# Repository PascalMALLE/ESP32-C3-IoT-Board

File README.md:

<<<<<<< HEAD
# ESP32-C3-IoT-Board
Board ESP32 IoT board for learning Kicad
=======
# ESP32-C3 IoT Development Board

A custom-designed IoT development board built around the **ESP32-C3-02**, featuring USB-C connectivity, Li-ion battery charging, environmental sensing, audio input, and removable storage.

## Project Overview

This project focuses on the design of a compact, custom PCB for IoT applications using KiCad. The board integrates wireless connectivity, power management, sensors, and data storage into a single hardware platform.

## Key Features

- **Microcontroller:** ESP32-C3-02 with Wi-Fi and Bluetooth Low Energy (BLE).
- **Power Management:** TP4056-based single-cell Li-ion battery charging.
- **USB-C:** USB connectivity and power input.
- **Environmental Sensing:** BME280 for temperature, humidity, and atmospheric pressure.
- **Audio Input:** Onboard microphone for sound acquisition.
- **Data Storage:** MicroSD card interface and additional flash memory.
- **Display Interface:** I²C interface for an optional OLED display.
- **Status Indicators:** LEDs for power and charging status.
- **Expansion:** Interfaces for additional sensors and peripherals.

## Hardware Design

### 1. Schematic

The schematic defines the electrical connections between the ESP32-C3-02, charging circuit, sensors, storage interfaces, and peripheral connectors.

### 2. PCB Layout

The PCB layout implements the circuit connections, component placement, routing, and board geometry.

| Front Side | Bottom Side |
|---|---|
|  |  |

### 3. 3D PCB Visualization

The 3D model provides a visual representation of the assembled PCB and component placement.

## Design Highlights

- Compact PCB layout designed in KiCad.
- USB-C and rechargeable Li-ion battery power options.
- Integrated wireless connectivity through the ESP32-C3.
- Sensor interfaces for environmental and audio data acquisition.
- MicroSD storage for data logging applications.
- Design files available for inspection and further development.

## Repository Contents

- **KiCad schematic:** `.kicad_sch`
- **KiCad PCB layout:** `.kicad_pcb`
- **3D visualizations:** PCB rendering images.
- **Gerber files:** Manufacturing output files, when included.
- **Bill of Materials (BOM):** Component list and procurement information.
- **Documentation:** Design screenshots and supporting resources.

## Tools

- KiCad
- PCB design and routing
- Electronic schematic capture
- 3D PCB visualization

## Potential Applications

- IoT environmental monitoring
- Portable data logging
- Wireless sensor nodes
- Embedded systems prototyping

## Project Status

PCB design and visualization completed. Hardware manufacturing, assembly, and functional validation should be documented as those stages are completed.

## Author

**Pascal Malle**

Electrical, Electronic and Telecommunications Engineering

---

*This project is intended for learning, prototyping, and further development. Verify the charging and battery-protection circuitry against the selected components' datasheets before manufacturing or powering the board.*
>>>>>>> 4541118 (Add ESP32-C3 IoT PCB design)

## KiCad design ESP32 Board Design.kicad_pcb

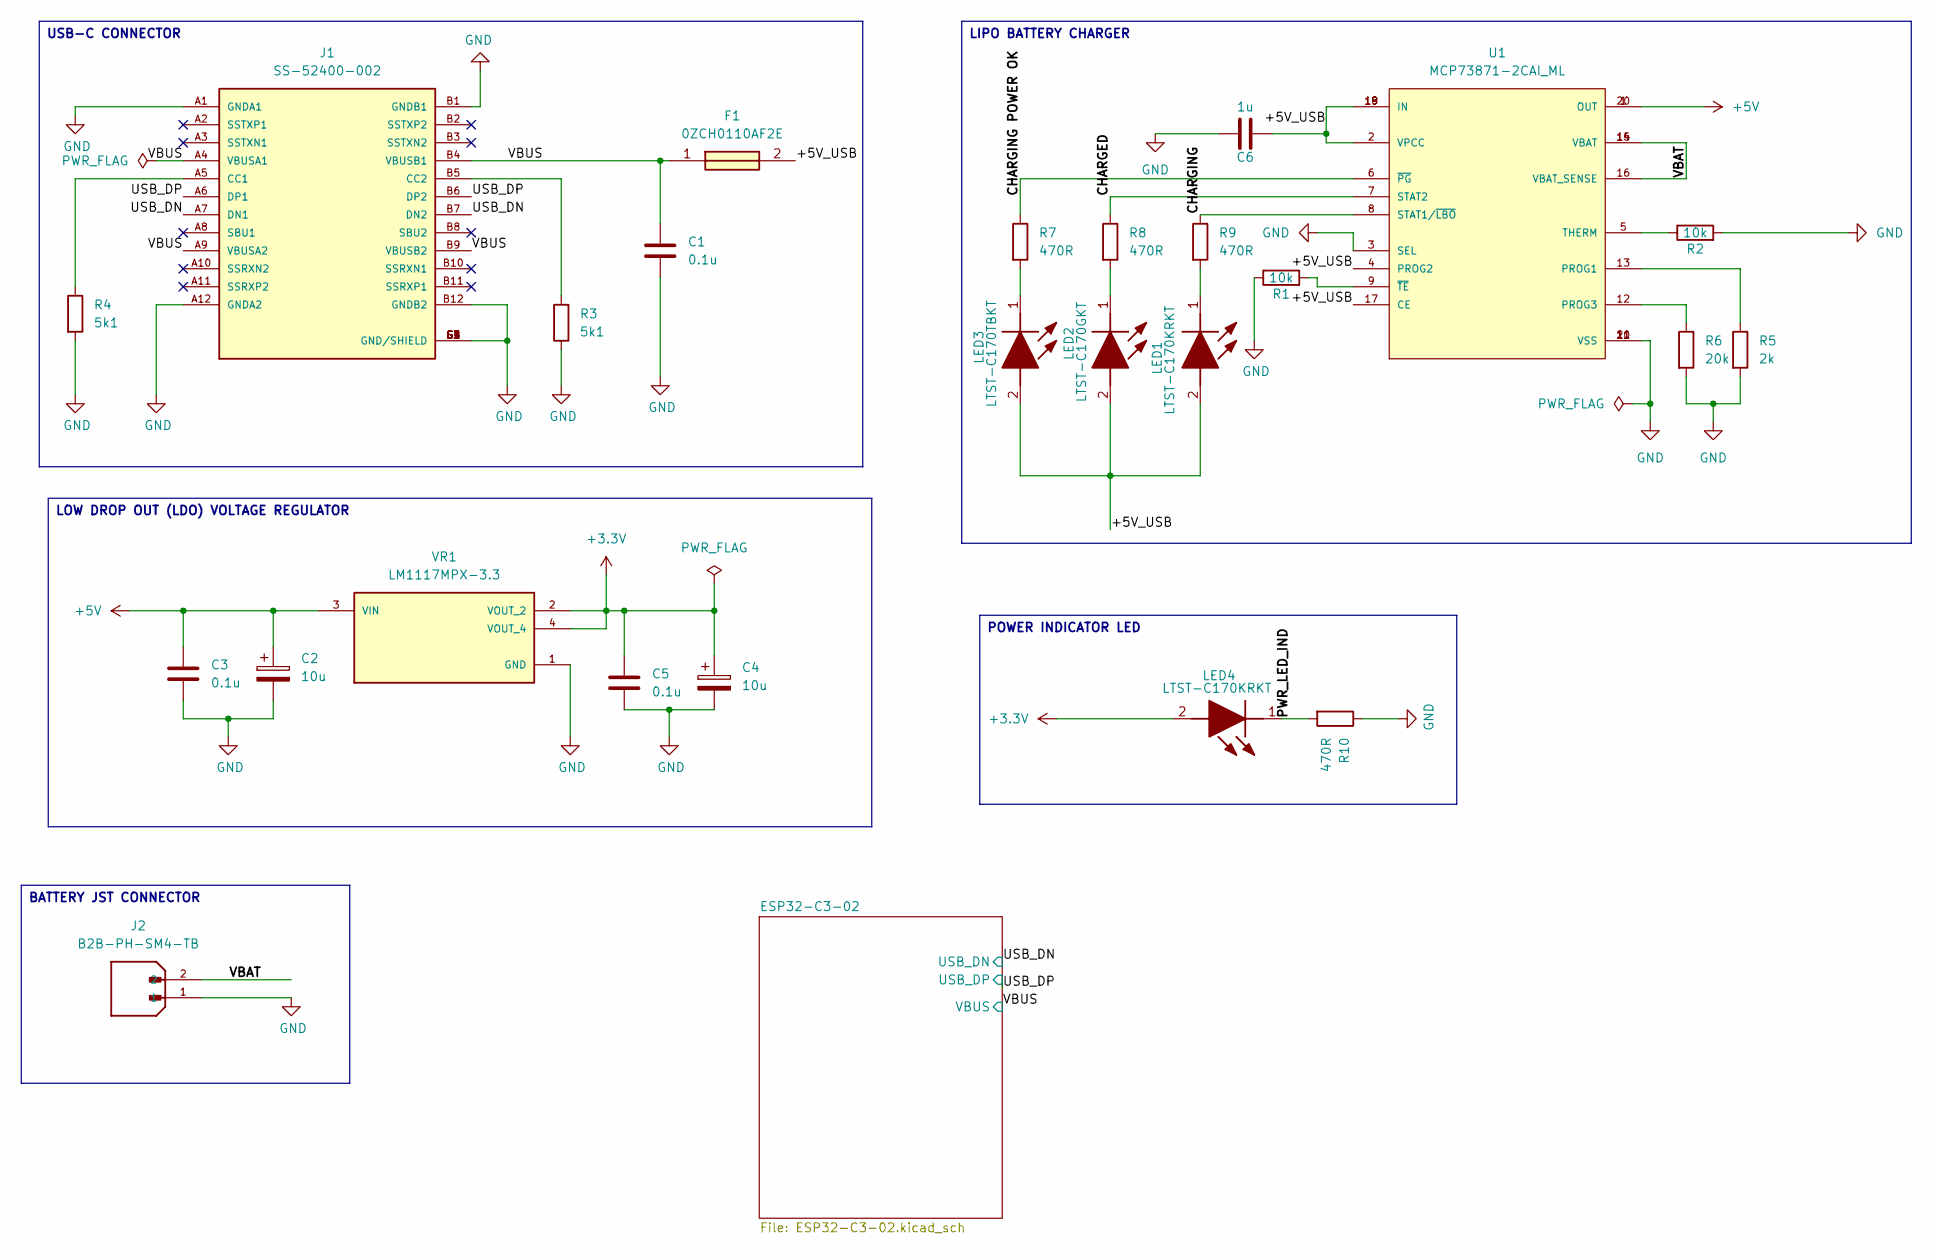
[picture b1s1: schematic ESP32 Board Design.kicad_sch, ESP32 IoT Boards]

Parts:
C1, C3, C5: 0.1u; C_0805_2012Metric
C2, C4: 10u; T491A
C6: 1u; C_0805_2012Metric
F1: 0ZCH0110AF2E; FUSC3226X100N; Manufacturer_Part_Number 0ZCH0110AF2E
J1: SS-52400-002; BELFUSE_SS-52400-002; PARTREV A0
J2: B2B-PH-SM4-TB; JST_B2B-PH-SM4-TB; PARTREV N/A
LED1, LED4: LTST-C170KRKT; LEDC2012X120N; Manufacturer_Part_Number LTST-C170KRKT; Mouser Part Number 859-LTST-C170KRKT
LED2: LTST-C170GKT; LEDC2012X120N; Manufacturer_Part_Number LTST-C170GKT; Mouser Part Number 859-LTST-C170GKT
LED3: LTST-C170TBKT; LEDC2012X120N; Manufacturer_Part_Number LTST-C170TBKT; Mouser Part Number 859-LTST-C170TBKT
R1, R2: 10k; R_0805_2012Metric
R3, R4: 5k1; R_0805_2012Metric
R5: 2k; R_0805_2012Metric
R6: 20k; R_0805_2012Metric
R7, R8, R9, R10: 470R; R_0805_2012Metric
U1: MCP73871-2CAI_ML; QFN50P400X400X100-21N; PARTREV D
VR1: LM1117MPX-3.3; VREG_LM1117MPX-3.3

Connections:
+3.3V: C4.1, C5.1, LED4.2 (A), VR1.2 (VOUT_2), VR1.4 (VOUT_4); also elsewhere on the board
+5V: C2.1, C3.1, U1.1 (OUT), U1.20 (OUT), VR1.3 (VIN)
/+5V_USB: C6.2, F1.2, LED1.2 (A), LED2.2 (A), LED3.2 (A), U1.2 (VPCC), U1.4 (PROG2), U1.17 (CE), U1.18 (IN), U1.19 (IN)
/CHARGED: R8.1, U1.7 (STAT2)
/CHARGING: R9.1, U1.8 (STAT1/~LBO)
/CHARGING POWER OK: R7.1, U1.6 (~PG)
/PWR_LED_IND: LED4.1 (K), R10.2; also elsewhere on the board
/USB_DN: J1.A7 (DN1), J1.B7 (DN2); also elsewhere on the board
/USB_DP: J1.A6 (DP1), J1.B6 (DP2); also elsewhere on the board
/VBAT: J2.2, U1.14 (VBAT), U1.15 (VBAT), U1.16 (VBAT_SENSE)
/VBUS: C1.1, F1.1, J1.A4 (VBUSA1), J1.A9 (VBUSA2), J1.B4 (VBUSB1), J1.B9 (VBUSB2); also elsewhere on the board
GND: C1.2, C2.2, C3.2, C4.2, C5.2, C6.1, J1.A1 (GNDA1), J1.A12 (GNDA2), J1.B1 (GNDB1), J1.B12 (GNDB2), J1.G1 (GND/SHIELD), J1.G2 (GND/SHIELD), J1.G3 (GND/SHIELD), J1.G4 (GND/SHIELD), J1.S1 (GND/SHIELD), J1.S2 (GND/SHIELD), J1.S3 (GND/SHIELD), J1.S4 (GND/SHIELD), J2.1, R1.1, R2.2, R3.1, R4.2, R5.2, R6.2, R10.1, U1.3 (SEL), U1.10 (VSS), U1.11 (VSS), U1.21 (VSS), VR1.1 (GND); also elsewhere on the board
unnamed: J1.A5 (CC1), R4.1
unnamed: J1.B5 (CC2), R3.2
unnamed: LED1.1 (K), R9.2
unnamed: LED2.1 (K), R8.2
unnamed: LED3.1 (K), R7.2
unnamed: R5.1, U1.13 (PROG1)
unnamed: R6.1, U1.12 (PROG3)
unnamed: R2.1, U1.5 (THERM)
unnamed: R1.2, U1.9 (~TE)

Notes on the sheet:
BATTERY JST CONNECTOR
USB-C CONNECTOR
LIPO BATTERY CHARGER
POWER INDICATOR LED
LOW DROP OUT (LDO) VOLTAGE REGULATOR

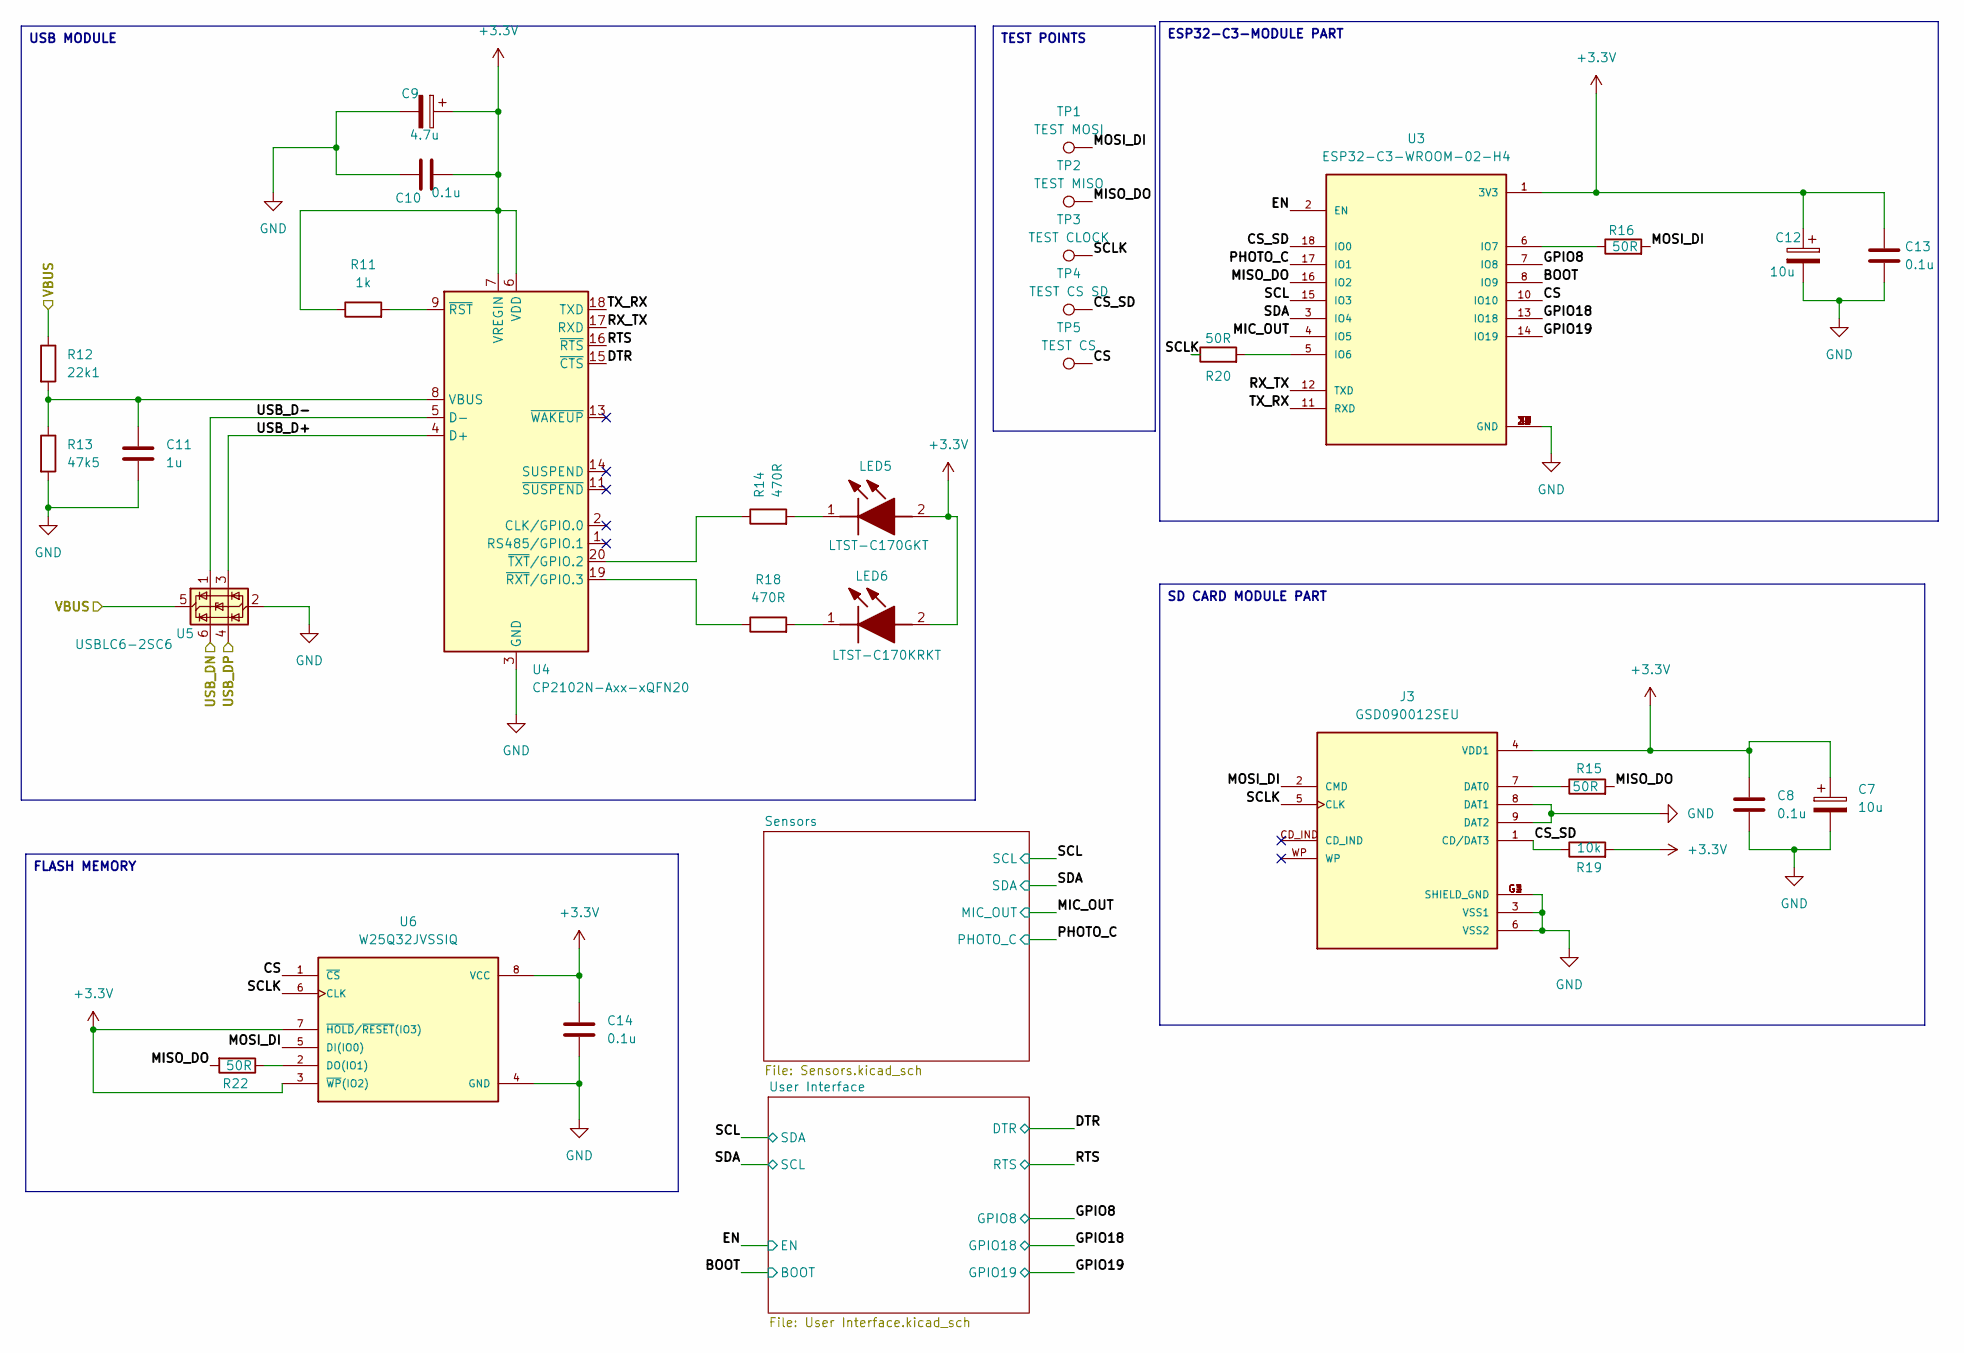
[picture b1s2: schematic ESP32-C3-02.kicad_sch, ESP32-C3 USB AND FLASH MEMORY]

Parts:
C7, C12: 10u; T491A
C8, C10, C13, C14: 0.1u; C_0805_2012Metric
C9: 4.7u; T491A
C11: 1u; C_0805_2012Metric
J3: GSD090012SEU; AMPHENOL_GSD090012SEU; PARTREV E
LED5: LTST-C170GKT; LEDC2012X120N; Manufacturer_Part_Number LTST-C170GKT; Mouser Part Number 859-LTST-C170GKT
LED6: LTST-C170KRKT; LEDC2012X120N; Manufacturer_Part_Number LTST-C170KRKT; Mouser Part Number 859-LTST-C170KRKT
R11: 1k; R_0805_2012Metric
R12: 22k1; R_0805_2012Metric
R13: 47k5; R_0805_2012Metric
R14, R18: 470R; R_0805_2012Metric
R15, R16, R20, R22: 50R; R_0805_2012Metric
R19: 10k; R_0805_2012Metric
TP1: TEST MOSI; TestPoint_Pad_D1.0mm
TP2: TEST MISO; TestPoint_Pad_D1.0mm
TP3: TEST CLOCK; TestPoint_Pad_D1.0mm
TP4: TEST CS SD; TestPoint_Pad_D1.0mm
TP5: TEST CS; TestPoint_Pad_D1.0mm
U3: ESP32-C3-WROOM-02-H4; MODULE_ESP32-C3-WROOM-02-H4
U4: CP2102N-Axx-xQFN20; SiliconLabs_QFN-20-1EP_3x3mm_P0.5mm_EP1.8x1.8mm
U5: USBLC6-2SC6; SOT-23-6
U6: W25Q32JVSSIQ; SOIC127P790X216-8N; M_PART_NUMBER W25QXX

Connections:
+3.3V: C7.1, C8.1, C9.1, C10.2, C12.1, C13.1, C14.1, J3.4 (VDD1), LED5.2 (A), LED6.2 (A), R11.1, R19.2, U3.1 (3V3), U4.6 (VDD), U4.7 (VREGIN), U6.3 (~WP(IO2)), U6.7 (~HOLD/~RESET(IO3)), U6.8 (VCC); also elsewhere on the board
/ESP32-C3-02/BOOT: U3.8 (IO9); also elsewhere on the board
/ESP32-C3-02/CS: TP5.1 (1_1), U3.10 (IO10), U6.1 (~CS)
/ESP32-C3-02/CS_SD: J3.1 (CD/DAT3), R19.1, TP4.1 (1_1), U3.18 (IO0)
/ESP32-C3-02/DTR: U4.15 (~CTS); also elsewhere on the board
/ESP32-C3-02/EN: U3.2 (EN); also elsewhere on the board
/ESP32-C3-02/GPIO8: U3.7 (IO8); also elsewhere on the board
/ESP32-C3-02/GPIO18: U3.13 (IO18); also elsewhere on the board
/ESP32-C3-02/GPIO19: U3.14 (IO19); also elsewhere on the board
/ESP32-C3-02/MIC_OUT: U3.4 (IO5); also elsewhere on the board
/ESP32-C3-02/MISO_DO: R15.2, R22.2, TP2.1 (1_1), U3.16 (IO2)
/ESP32-C3-02/MOSI_DI: J3.2 (CMD), R16.2, TP1.1 (1_1), U6.5 (DI(IO0))
/ESP32-C3-02/PHOTO_C: U3.17 (IO1); also elsewhere on the board
/ESP32-C3-02/RTS: U4.16 (~RTS); also elsewhere on the board
/ESP32-C3-02/RX_TX: U3.12 (TXD), U4.17 (RXD)
/ESP32-C3-02/SCL: U3.15 (IO3); also elsewhere on the board
/ESP32-C3-02/SCLK: J3.5 (CLK), R20.1, TP3.1 (1_1), U6.6 (CLK)
/ESP32-C3-02/SDA: U3.3 (IO4); also elsewhere on the board
/ESP32-C3-02/TX_RX: U3.11 (RXD), U4.18 (TXD)
/ESP32-C3-02/USB_D+: U4.4 (D+), U5.3 (I/O2)
/ESP32-C3-02/USB_D-: U4.5 (D-), U5.1 (I/O1)
/USB_DN: U5.6 (I/O1); also elsewhere on the board
/USB_DP: U5.4 (I/O2); also elsewhere on the board
/VBUS: R12.1, U5.5 (VBUS); also elsewhere on the board
GND: C7.2, C8.2, C9.2, C10.1, C11.2, C12.2, C13.2, C14.2, J3.3 (VSS1), J3.6 (VSS2), J3.8 (DAT1), J3.9 (DAT2), J3.G1 (SHIELD_GND), J3.G2 (SHIELD_GND), J3.G3 (SHIELD_GND), J3.G4 (SHIELD_GND), R13.2, U3.9 (GND), U3.19 (GND), U3.20 (GND), U3.21 (GND), U3.22 (GND), U3.23 (GND), U3.24 (GND), U3.25 (GND), U3.26 (GND), U3.27 (GND), U3.28 (GND), U3.29 (GND), U3.30 (GND), U3.31 (GND), U3.32 (GND), U3.33 (GND), U3.34 (GND), U3.35 (GND), U3.36 (GND), U3.37 (GND), U3.38 (GND), U3.39 (GND), U4.3 (GND), U4.12 (GND), U4.21 (GND), U5.2 (GND), U6.4 (GND); also elsewhere on the board
unnamed: J3.7 (DAT0), R15.1
unnamed: LED5.1 (K), R14.2
unnamed: LED6.1 (K), R18.2
unnamed: R20.2, U3.5 (IO6)
unnamed: R16.1, U3.6 (IO7)
unnamed: C11.1, R12.2, R13.1, U4.8 (VBUS)
unnamed: R11.2, U4.9 (~RST)
unnamed: R18.1, U4.19 (~RXT/GPIO.3)
unnamed: R14.1, U4.20 (~TXT/GPIO.2)
unnamed: R22.1, U6.2 (DO(IO1))

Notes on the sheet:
ESP32-C3-MODULE PART
TEST POINTS
FLASH MEMORY
SD CARD MODULE PART
USB MODULE

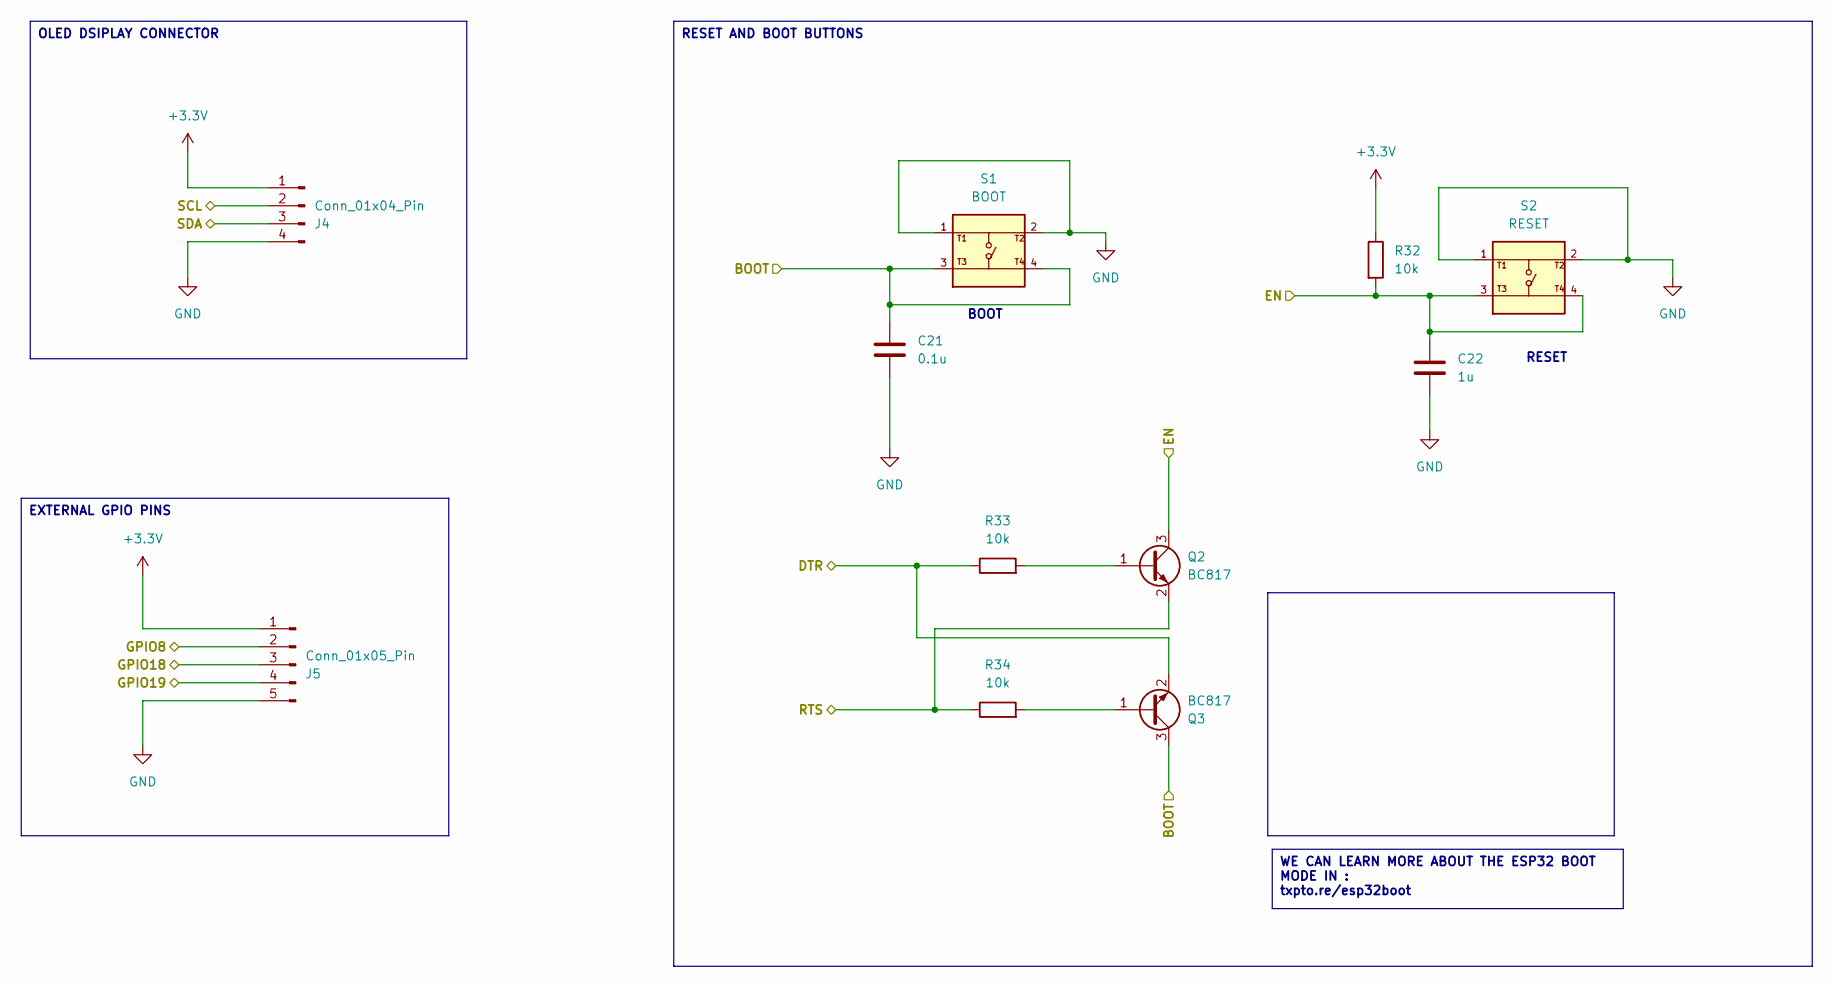
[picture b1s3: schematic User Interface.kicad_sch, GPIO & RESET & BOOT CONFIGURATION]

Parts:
C21: 0.1u; C_0805_2012Metric
C22: 1u; C_0805_2012Metric
J4: Conn_01x04_Pin; PinHeader_1x04_P2.54mm_Vertical
J5: Conn_01x05_Pin; PinHeader_1x05_P2.54mm_Vertical
Q2, Q3: BC817; SOT-23
R32, R33, R34: 10k; R_0805_2012Metric
S1: BOOT; SW_USLPT2819DT2TR; PARTREV P
S2: RESET; SW_USLPT2819DT2TR; PARTREV P

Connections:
+3.3V: J4.1, J5.1, R32.1; also elsewhere on the board
/ESP32-C3-02/BOOT: C21.1, Q3.3 (C), S1.3, S1.4; also elsewhere on the board
/ESP32-C3-02/DTR: Q3.2 (E), R33.1; also elsewhere on the board
/ESP32-C3-02/EN: C22.1, Q2.3 (C), R32.2, S2.3, S2.4; also elsewhere on the board
/ESP32-C3-02/GPIO8: J5.2; also elsewhere on the board
/ESP32-C3-02/GPIO18: J5.3; also elsewhere on the board
/ESP32-C3-02/GPIO19: J5.4; also elsewhere on the board
/ESP32-C3-02/RTS: Q2.2 (E), R34.1; also elsewhere on the board
/ESP32-C3-02/SCL: J4.3; also elsewhere on the board
/ESP32-C3-02/SDA: J4.2; also elsewhere on the board
GND: C21.2, C22.2, J4.4, J5.5, S1.1, S1.2, S2.1, S2.2; also elsewhere on the board
unnamed: Q2.1 (B), R33.2
unnamed: Q3.1 (B), R34.2

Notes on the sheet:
BOOT
RESET
OLED DSIPLAY CONNECTOR
EXTERNAL GPIO PINS
WE CAN LEARN MORE ABOUT THE ESP32 BOOT MODE IN : txpto.re/esp32boot
RESET AND BOOT BUTTONS

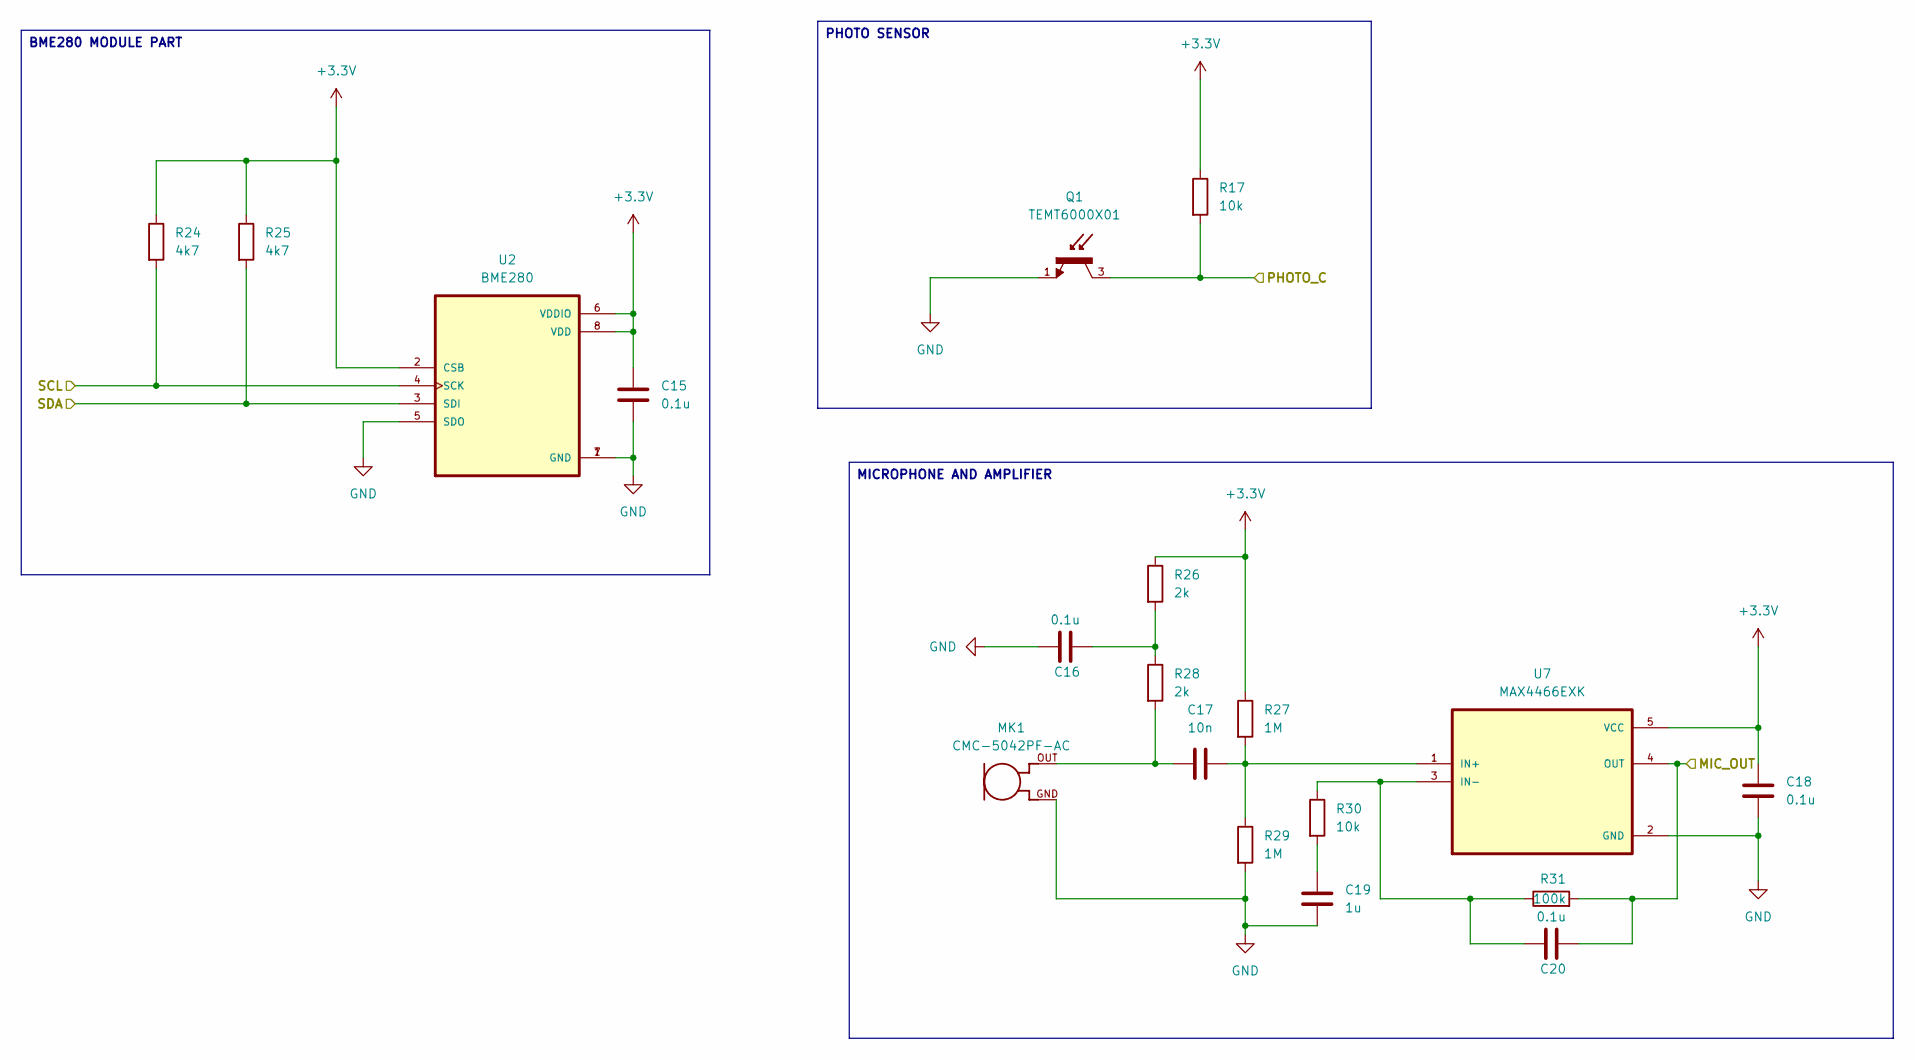
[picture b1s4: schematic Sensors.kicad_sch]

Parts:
C15, C16, C18, C20: 0.1u; C_0805_2012Metric
C17: 10n; C_0805_2012Metric
C19: 1u; C_0805_2012Metric
MK1: CMC-5042PF-AC; CUI_CMC-5042PF-AC
Q1: TEMT6000X01; TRANS_TEMT6000X01; PARTREV 1.9
R17, R30: 10k; R_0805_2012Metric
R24, R25: 4k7; R_0805_2012Metric
R26, R28: 2k; R_0805_2012Metric
R27, R29: 1M; R_0805_2012Metric
R31: 100k; R_0805_2012Metric
U2: BME280; PSON65P250X250X100-8N
U7: MAX4466EXK; SOT65P210X110-5N

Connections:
+3.3V: C15.1, C18.1, R17.1, R24.1, R25.1, R26.1, R27.1, U2.2 (CSB), U2.6 (VDDIO), U2.8 (VDD), U7.5 (VCC); also elsewhere on the board
/ESP32-C3-02/MIC_OUT: C20.2, R31.2, U7.4 (OUT); also elsewhere on the board
/ESP32-C3-02/PHOTO_C: Q1.3, R17.2; also elsewhere on the board
/ESP32-C3-02/SCL: R24.2, U2.4 (SCK); also elsewhere on the board
/ESP32-C3-02/SDA: R25.2, U2.3 (SDI); also elsewhere on the board
GND: C15.2, C16.1, C18.2, C19.2, MK1.GND, Q1.1, R29.2, U2.1 (GND), U2.5 (SDO), U2.7 (GND), U7.2 (GND); also elsewhere on the board
unnamed: C16.2, R26.2, R28.1
unnamed: C17.1, MK1.OUT, R28.2
unnamed: C19.1, R30.2
unnamed: C17.2, R27.2, R29.1, U7.1 (IN+)
unnamed: C20.1, R30.1, R31.1, U7.3 (IN-)

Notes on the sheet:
BME280 MODULE PART
MICROPHONE AND AMPLIFIER
PHOTO SENSOR

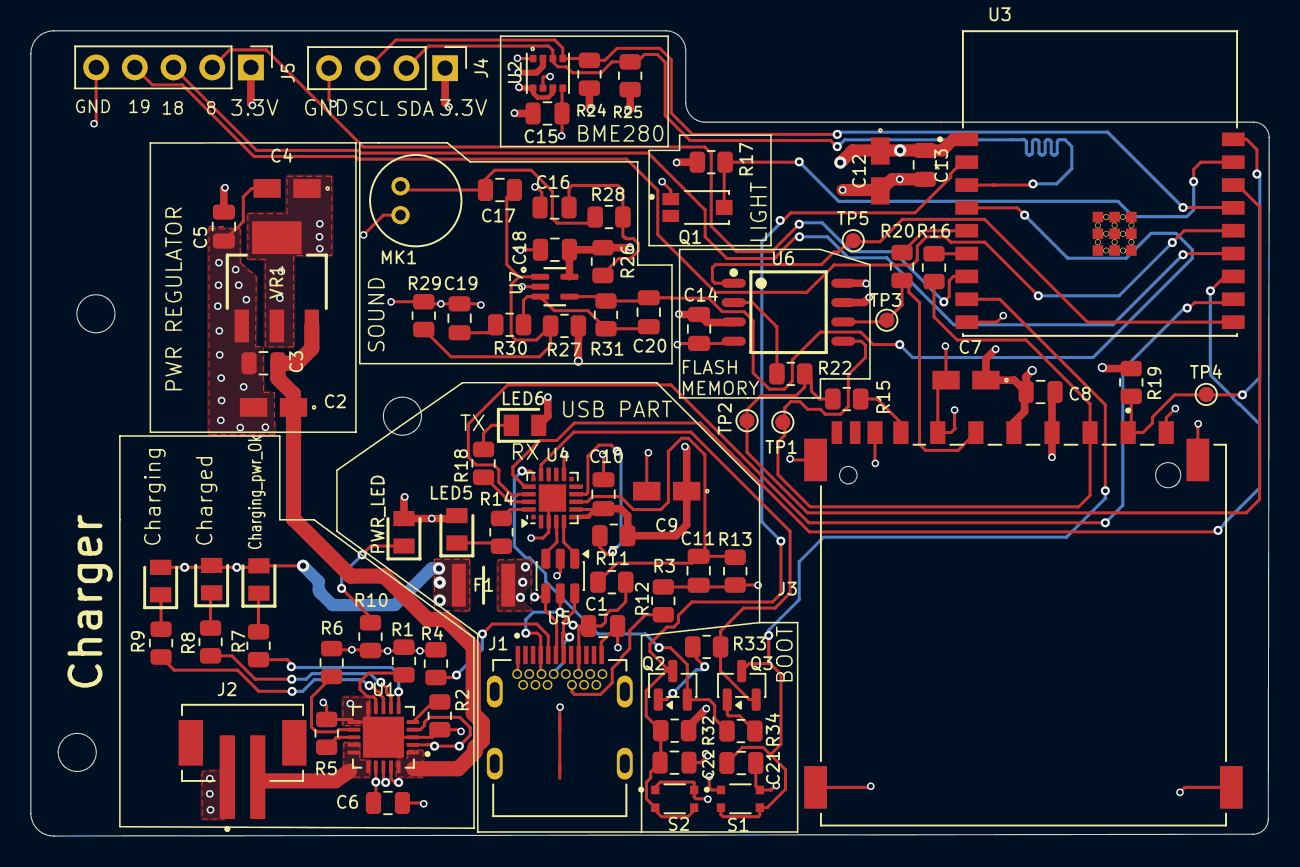
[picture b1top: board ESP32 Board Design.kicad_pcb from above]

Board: 4 copper layers, 81.3 x 52.9 mm, 85 parts (0 on the bottom side), 58 nets.

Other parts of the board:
PWR_LED: LTST-C170KRKT; LEDC2012X120N

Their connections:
+3.3V: PWR_LED.2 (A); also elsewhere on the board
/PWR_LED_IND: PWR_LED.1 (K); also elsewhere on the board
